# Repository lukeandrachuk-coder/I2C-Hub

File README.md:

The purpose of this project is to make a board that expands the number of I2C connective devices that you can connect to a microcontroller. The board was designed in KiCAD a free PCB design software. How you use it is you connect the VCC, GND, SCL, and SDA from your microcontroller to the same ports in the I2C_In pins on the I2C hub board. You can then connect one or more of the eight out pins to your I2C devices.
It works by taking the input signal and based on the I2C address given sends it to the corresponding device if it egsists.

# Assembly instructions: 
  First the TCA9546APWR chip needs to be soldered to the board. I recommend using solder paste for this as it is a surface-mount device. 

  Next solder the corresponding resistors in their places as well as the ceramic capacitor and LED. Lastly, solder the male pin headers into their spots. You should have nine 4-pin headers, and three 3-pin headers. 

  The 3-pin headers allow you to change the I2C address of the board based on which endpin you connect to the centre. One will pull it low (0), and the other will pull it high (1), letting you very the I2C address so it does not get confused with other I2C boards in code.

# BOM

You must order the PCB from JLCPCB*. The link I have provided takes you to the online PCB quote page. You must upload the provided greber files .zip then select the PCB colour you want (any colour exept green takes longer to ship). You can leave all the other options alone.

<table>
  <thead>
    <tr>
      <th style="border: 1px solid #dddddd; padding: 8px; text-align: left;">Item</th>
      <th style="border: 1px solid #dddddd; padding: 8px; text-align: left;">Qty</th>
      <th style="border: 1px solid #dddddd; padding: 8px; text-align: left;">Supplier</th>
      <th style="border: 1px solid #dddddd; padding: 8px; text-align: left;">Cost/item</th>
      <th style="border: 1px solid #dddddd; padding: 8px; text-align: left;">Total Cost</th>
      <th style="border: 1px solid #dddddd; padding: 8px; text-align: left;">link</th>
    </tr>
  <thead>
  <tbody>
     <tr>
      <td style="border: 1px solid #dddddd; padding: 8px;">I2C Hub PCB</td>
      <td style="border: 1px solid #dddddd; padding: 8px;">5</td>
      <td style="border: 1px solid #dddddd; padding: 8px;">JLCPCB</td>
      <td style="border: 1px solid #dddddd; padding: 8px;">N/A</td>
      <td style="border: 1px solid #dddddd; padding: 8px;">$5.61</td>
      <td style="border: 1px solid #dddddd; padding: 8px;">https://cart.jlcpcb.com/quote?from=pcbassembly_page</td>
    </tr>
    <tr>
      <td style="border: 1px solid #dddddd; padding: 8px;">TCA9546APWR</td>
      <td style="border: 1px solid #dddddd; padding: 8px;">5</td>
      <td style="border: 1px solid #dddddd; padding: 8px;">Digikey</td>
      <td style="border: 1px solid #dddddd; padding: 8px;">$2.12</td>
      <td style="border: 1px solid #dddddd; padding: 8px;">$10.60</td>
      <td style="border: 1px solid #dddddd; padding: 8px;">https://www.digikey.ca/en/products/detail/texas-instruments/TCA9546APWR/4842201</td>
    </tr>
     <tr>
      <td style="border: 1px solid #dddddd; padding: 8px;">2.54mm male pin headers</td>
      <td style="border: 1px solid #dddddd; padding: 8px;">1</td>
      <td style="border: 1px solid #dddddd; padding: 8px;">Amazon</td>
      <td style="border: 1px solid #dddddd; padding: 8px;">$3.59</td>
      <td style="border: 1px solid #dddddd; padding: 8px;">$3.59</td>
      <td style="border: 1px solid #dddddd; padding: 8px;">https://www.amazon.ca/2-54mm-Single-Socket-Breakaway-Connectors/dp/B0H9M69F4F/ref=sr_1_28?dib=eyJ2IjoiMSJ9.yTvO4Ctxl0OUyRyW3pki7Tqhjb_15nBXmuAJZeGEDNMo0eCxgBYOPyxYXSXgiYb4ljKhB2EOc_AQCAfljvOxCJ1Xxm2OkeHzCJ0IBh2KbvS-aUOyQDNqCzc6Uboud4w_PwxPd1CnfKyz1QM7oZLSZMhPvx28IleQ-zvfp2LupoBJt2vVJot_V8wWuBBqPMD4x6SXMQZKH2Puiv3ejK01JE38yJ67acV-_RkHXEawoAUQtakQwPXnNQur8iJZCgJsKgFyXAcIHZpj9kGQyyEAC8b53asezkW5_Me8TBcmNrY.DG0-hsSwsN1YIFz_b5xScE9tyFhYPBRk2B2CW9RvPzQ&dib_tag=se&gad_source=1&hvadid=788542685418&hvdev=c&hvexpln=0&hvlocphy=9189569&hvnetw=g&hvocijid=1598390221780357774--&hvqmt=b&hvrand=1598390221780357774&hvtargid=kwd-2493940636015&hydadcr=28046_14944998&keywords=2.54+mm+male+header+pins&mcid=5f4d9b8a47033eab997e191b3ade675b&qid=1791668972&refinements=p_36%3A-1000&rnid=12035759011&sr=8-28</td>
    </tr>
    <tr>
      <td style="border: 1px solid #dddddd; padding: 8px;">K104K15X7RF5TL2</td>
      <td style="border: 1px solid #dddddd; padding: 8px;">5</td>
      <td style="border: 1px solid #dddddd; padding: 8px;">Digikey</td>
      <td style="border: 1px solid #dddddd; padding: 8px;">$0.43</td>
      <td style="border: 1px solid #dddddd; padding: 8px;">$2.15</td>
      <td style="border: 1px solid #dddddd; padding: 8px;">https://www.digikey.ca/en/products/detail/vishay-beyschlag-draloric-bc-components/K104K15X7RF5TL2/286538</td>
    </tr>
      <tr>
      <td style="border: 1px solid #dddddd; padding: 8px;">CF14JT4K70</td>
      <td style="border: 1px solid #dddddd; padding: 8px;">10</td>
      <td style="border: 1px solid #dddddd; padding: 8px;">Digikey</td>
      <td style="border: 1px solid #dddddd; padding: 8px;">$0.04</td>
      <td style="border: 1px solid #dddddd; padding: 8px;">$0.40</td>
      <td style="border: 1px solid #dddddd; padding: 8px;">https://www.digikey.ca/en/products/detail/stackpole-electronics-inc/CF14JT4K70/1741428</td>
    </tr>
  </tbody>
<table>

  Plus tax and shipping.

  *I have chosen JLCPCB but you can use any manufacturer you want.

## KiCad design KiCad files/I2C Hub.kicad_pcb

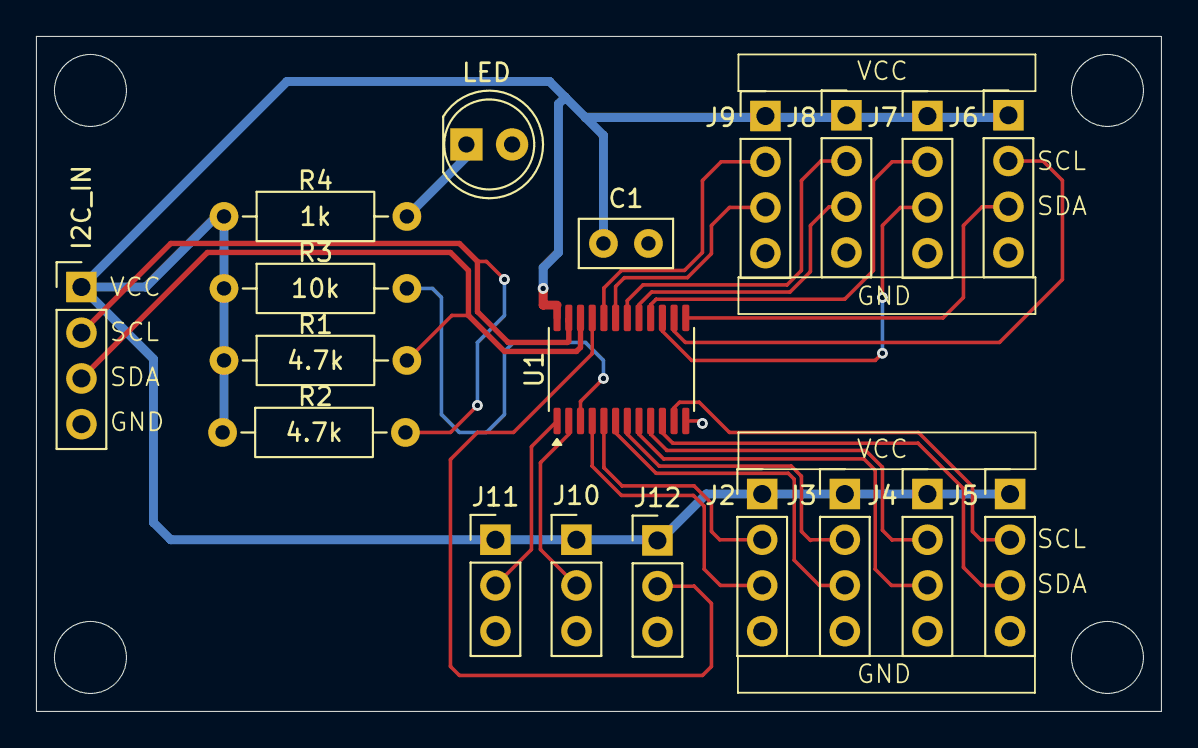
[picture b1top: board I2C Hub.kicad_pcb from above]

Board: 2 copper layers, 62.5 x 37.5 mm, 19 parts (0 on the bottom side), 25 nets.

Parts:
C1: 0.1uF; C_Disc_D5.0mm_W2.5mm_P2.50mm
D1: LED; LED_D5.0mm
J1: I2C_IN; PinHeader_1x04_P2.54mm_Vertical
J2: I2C_OUT_0; PinHeader_1x04_P2.54mm_Vertical
J3: I2C_OUT_1; PinHeader_1x04_P2.54mm_Vertical
J4: I2C_OUT_2; PinHeader_1x04_P2.54mm_Vertical
J5: I2C_OUT_3; PinHeader_1x04_P2.54mm_Vertical
J6: 4; PinHeader_1x04_P2.54mm_Vertical
J7: I2C_OUT_5; PinHeader_1x04_P2.54mm_Vertical
J8: I2C_OUT_6; PinHeader_1x04_P2.54mm_Vertical
J9: I2C_OUT_7; PinHeader_1x04_P2.54mm_Vertical
J10, J11, J12: Conn_01x03_Pin; PinHeader_1x03_P2.54mm_Vertical
R1, R2: 4.7k; R_Axial_DIN0207_L6.3mm_D2.5mm_P10.16mm_Horizontal
R3: 10k; R_Axial_DIN0207_L6.3mm_D2.5mm_P10.16mm_Horizontal
R4: 1k; R_Axial_DIN0207_L6.3mm_D2.5mm_P10.16mm_Horizontal
U1: TCA9548APWR; TSSOP-24_4.4x7.8mm_P0.65mm

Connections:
GND: C1.2, D1.2 (A), J1.4, J2.4, J3.4, J4.4, J5.4, J6.4, J7.4, J8.4, J9.4, J10.3, J11.3, J12.3, U1.12 (GND)
LED: D1.1 (K), R4.2
unnamed: J1.2, R2.2, U1.23 (SDA)
unnamed: J1.3, R1.2, U1.22 (SCL)
unnamed: J2.2, U1.5 (SC0)
unnamed: J2.3, U1.4 (SD0)
unnamed: J3.2, U1.7 (SC1)
unnamed: J3.3, U1.6 (SD1)
unnamed: J4.2, U1.9 (SC2)
unnamed: J4.3, U1.8 (SD2)
unnamed: J5.2, U1.11 (SC3)
unnamed: J5.3, U1.10 (SD3)
unnamed: J6.2, U1.14 (SC4)
unnamed: J6.3, U1.13 (SD4)
unnamed: J7.2, U1.16 (SC5)
unnamed: J7.3, U1.15 (SD5)
unnamed: J8.2, U1.18 (SC6)
unnamed: J8.3, U1.17 (SD6)
unnamed: J9.2, U1.20 (SC7)
unnamed: J9.3, U1.19 (SD7)
unnamed: J10.2, U1.2 (A1)
unnamed: J11.2, U1.1 (A0)
unnamed: J12.2, U1.21 (A2)
unnamed: R3.2, U1.3 (~RESET)
VCC: C1.1, J1.1, J2.1, J3.1, J4.1, J5.1, J6.1, J7.1, J8.1, J9.1, J10.1, J11.1, J12.1, R1.1, R2.1, R3.1, R4.1, U1.24 (VCC)
